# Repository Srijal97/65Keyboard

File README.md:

# 65Keyboard
Making a 65% Mechanical Keyboard

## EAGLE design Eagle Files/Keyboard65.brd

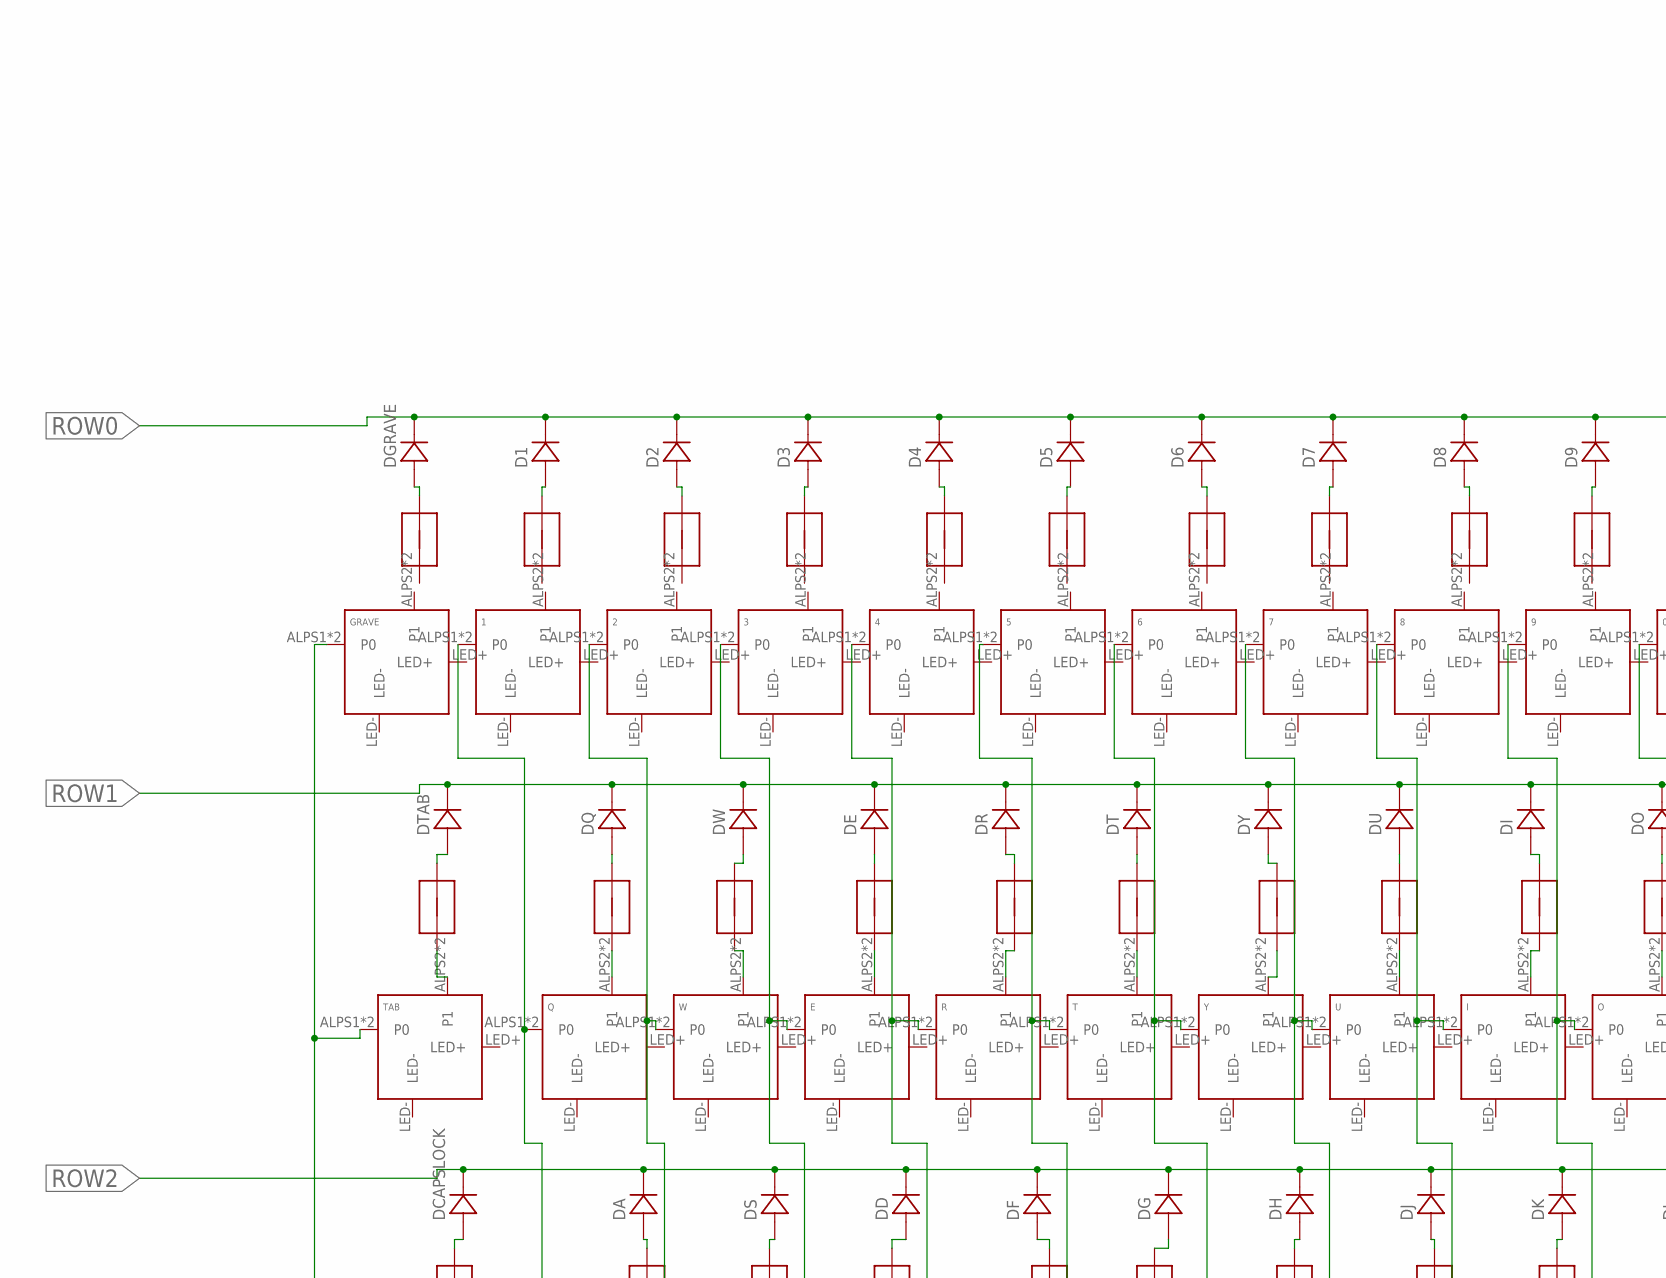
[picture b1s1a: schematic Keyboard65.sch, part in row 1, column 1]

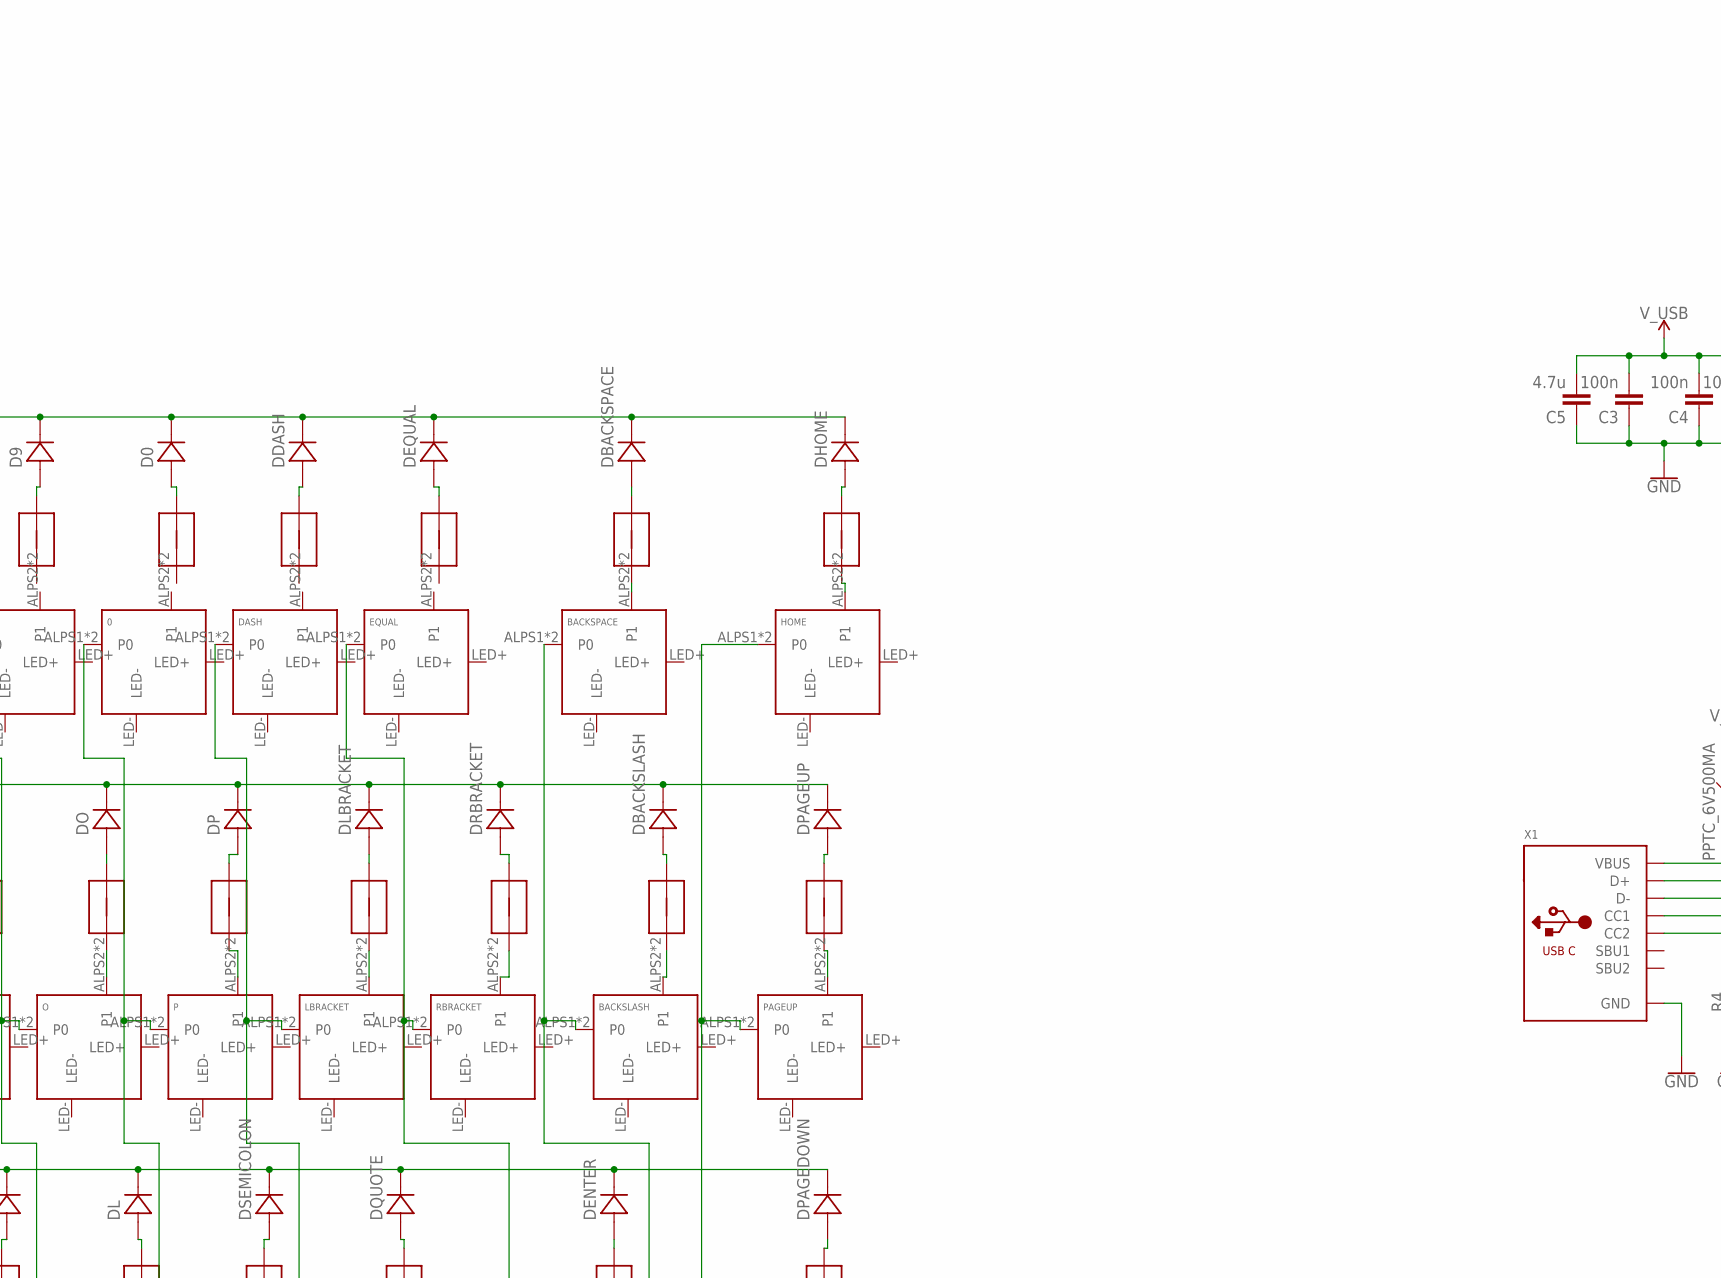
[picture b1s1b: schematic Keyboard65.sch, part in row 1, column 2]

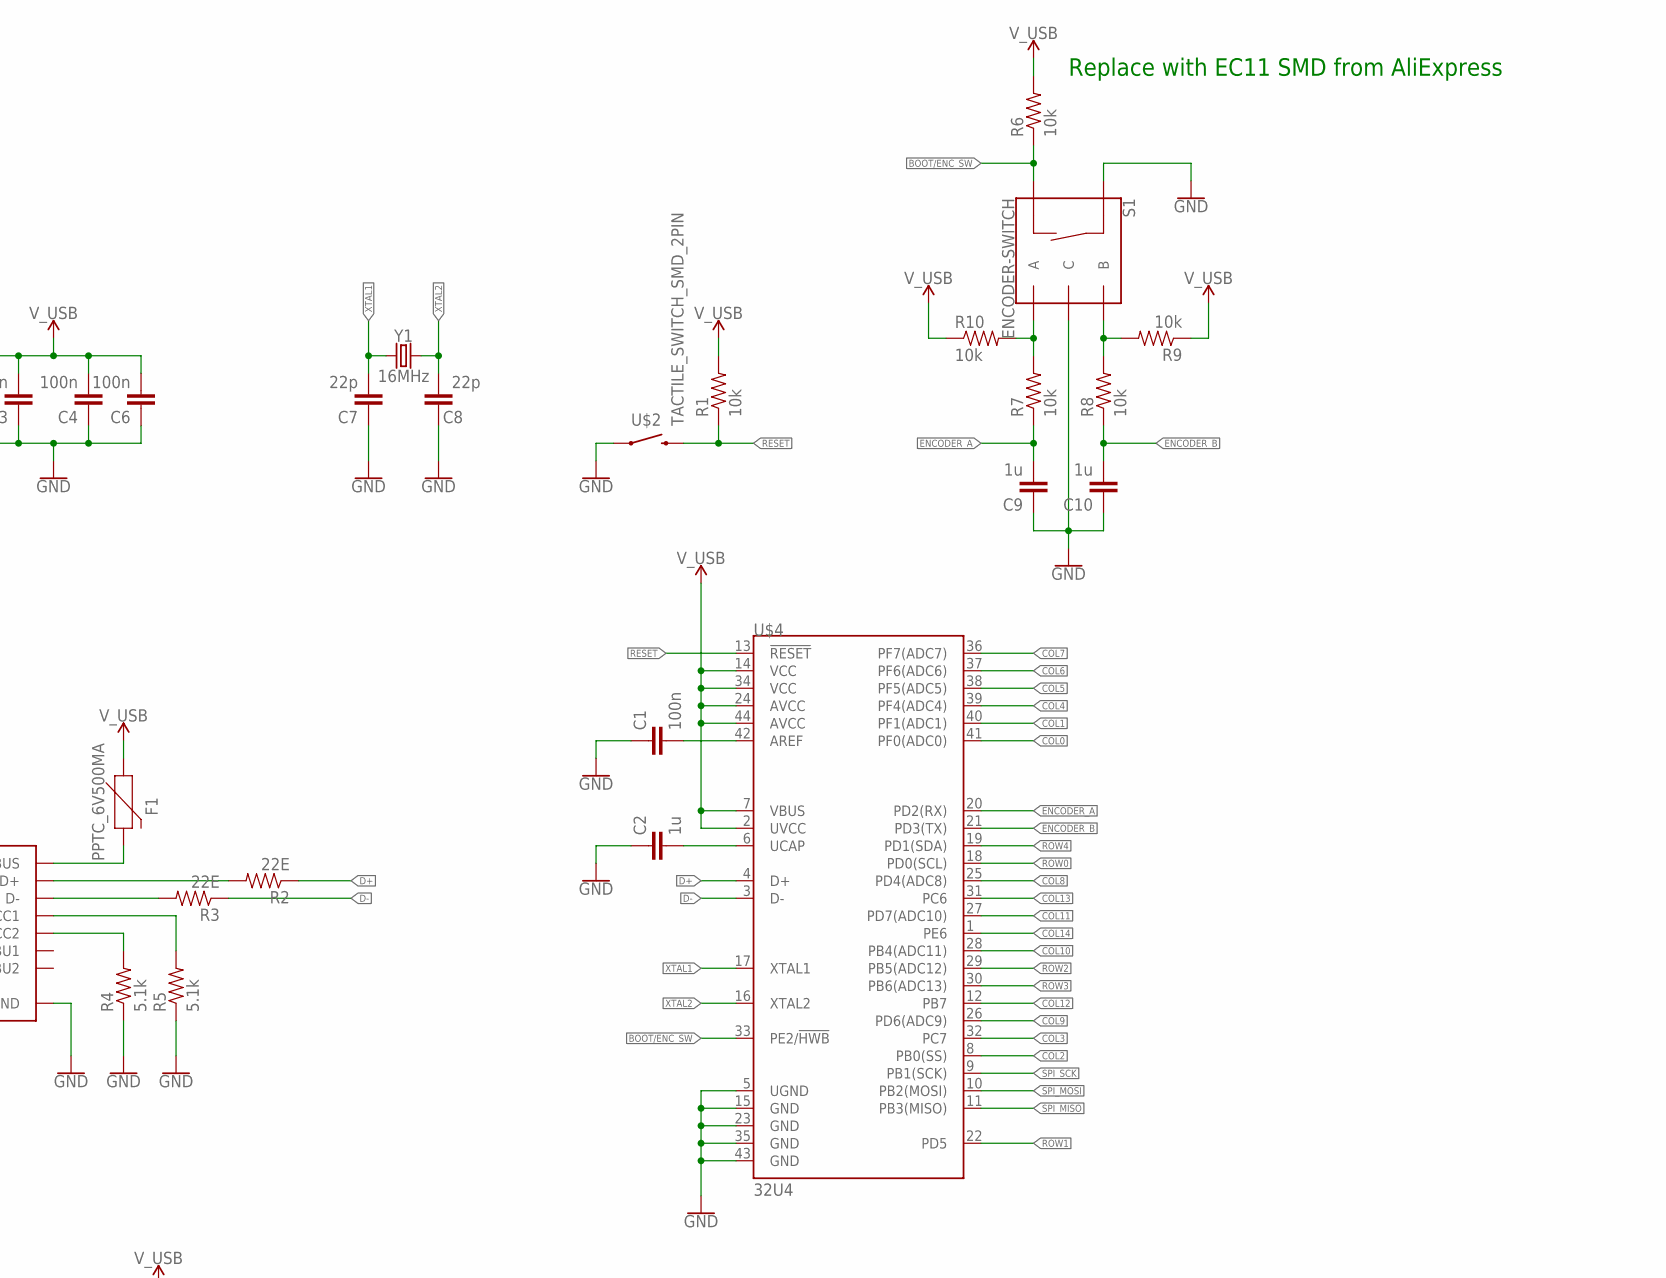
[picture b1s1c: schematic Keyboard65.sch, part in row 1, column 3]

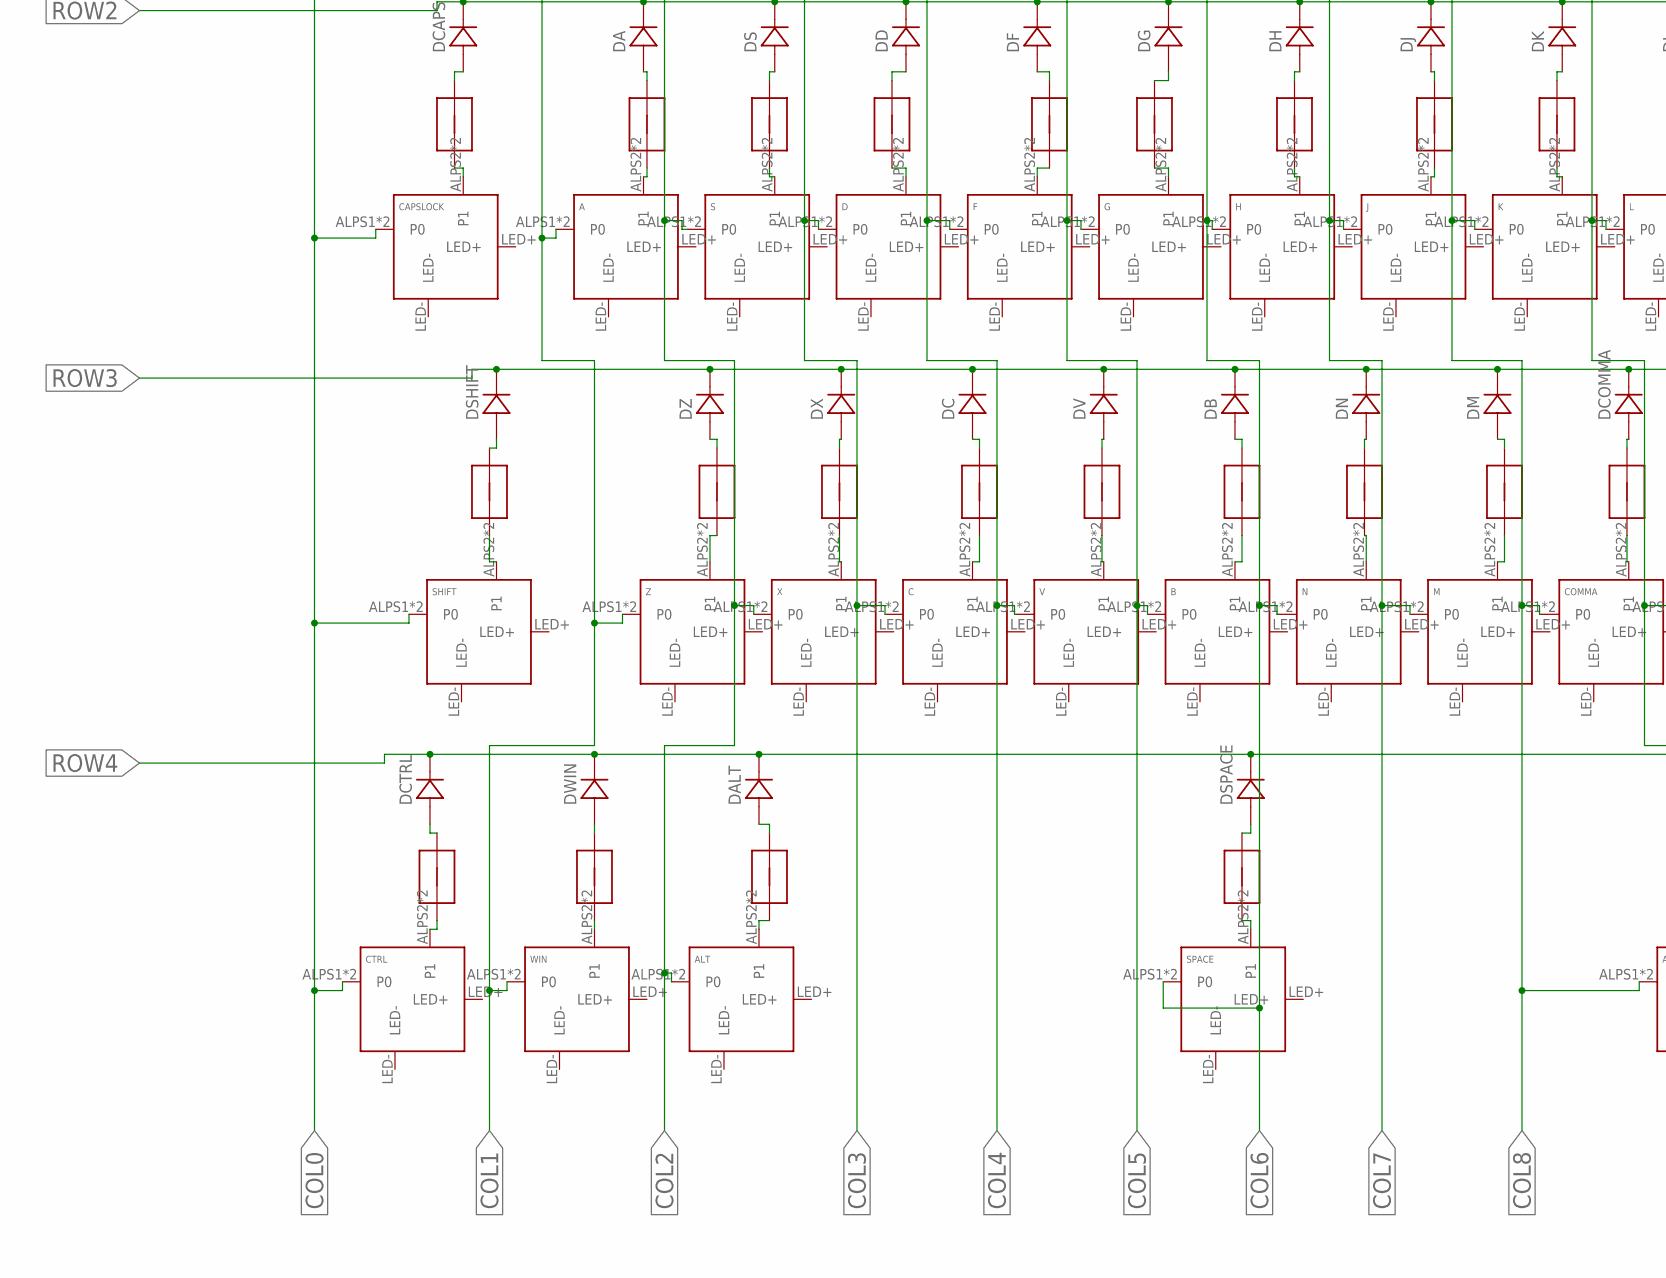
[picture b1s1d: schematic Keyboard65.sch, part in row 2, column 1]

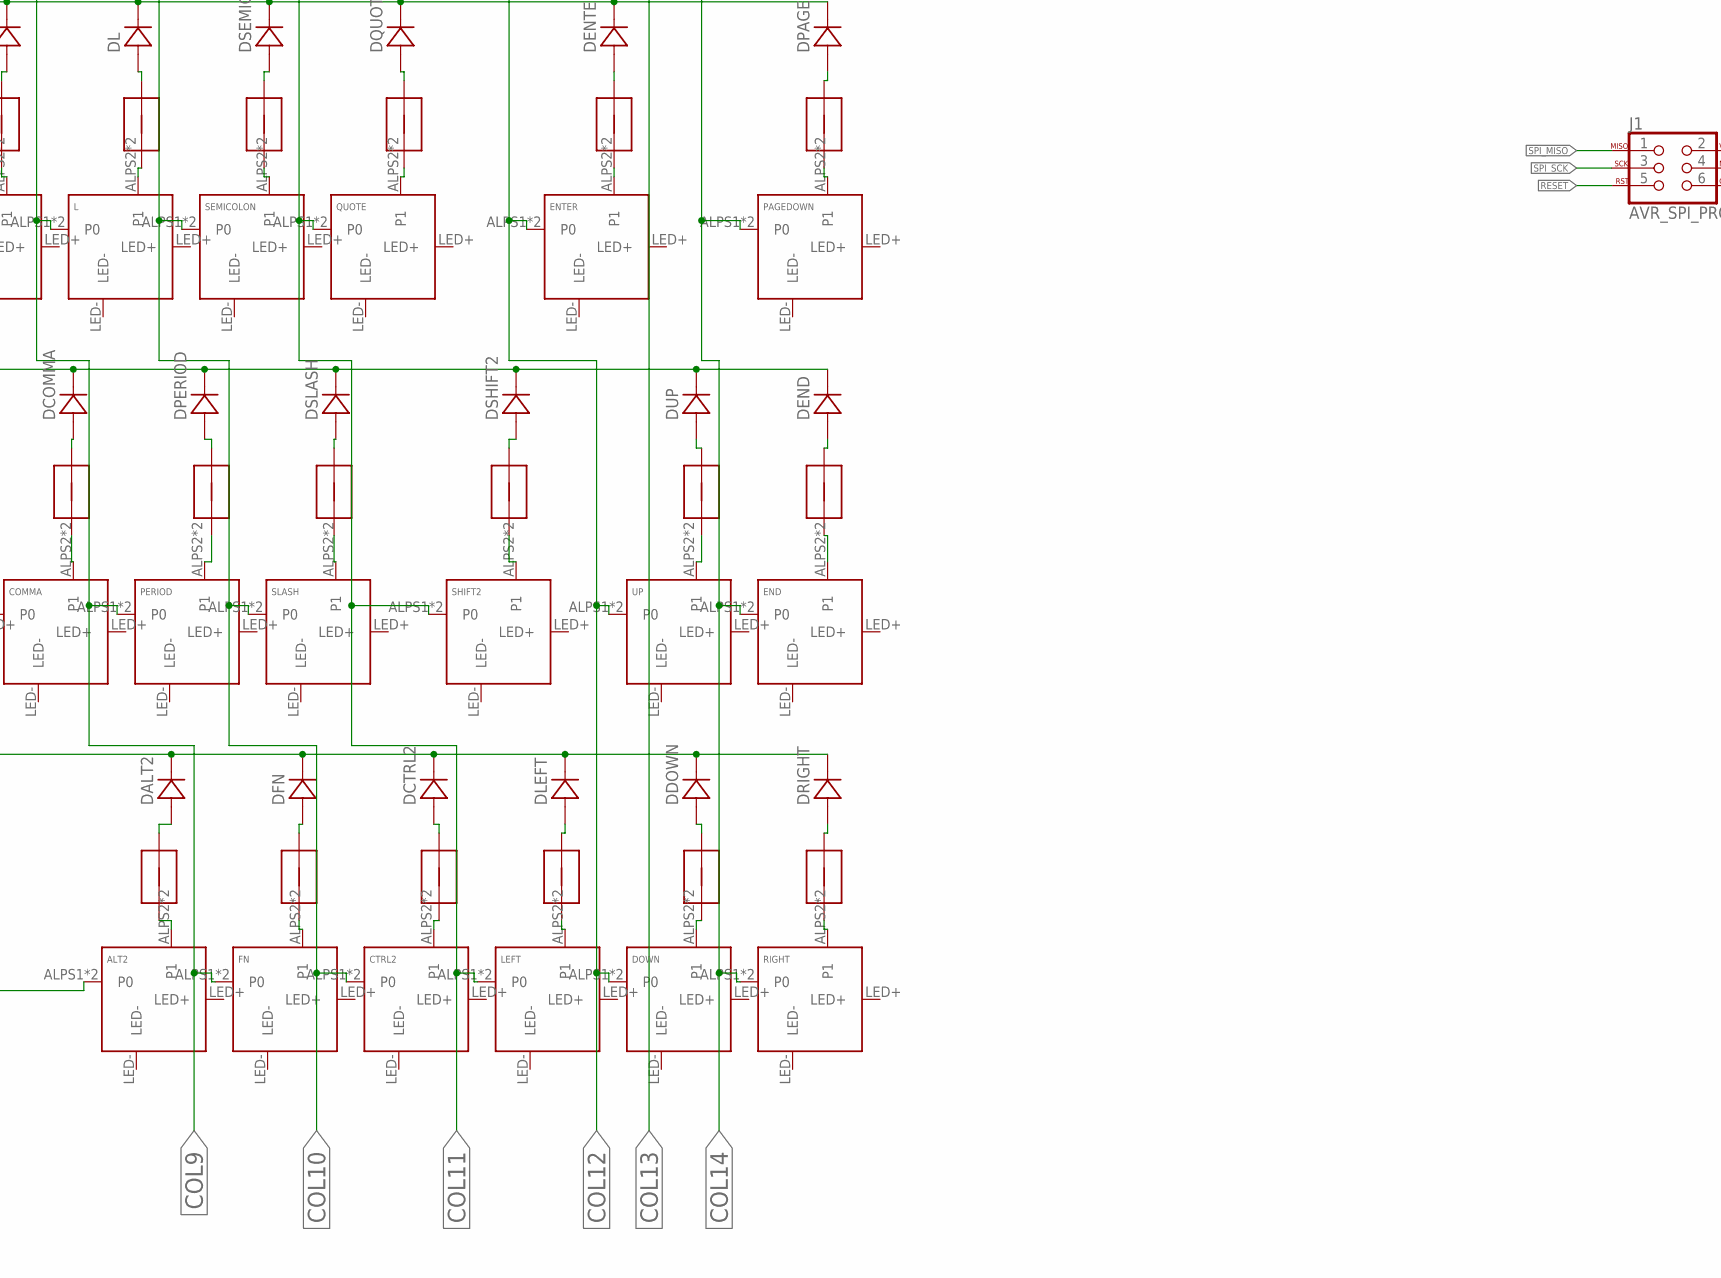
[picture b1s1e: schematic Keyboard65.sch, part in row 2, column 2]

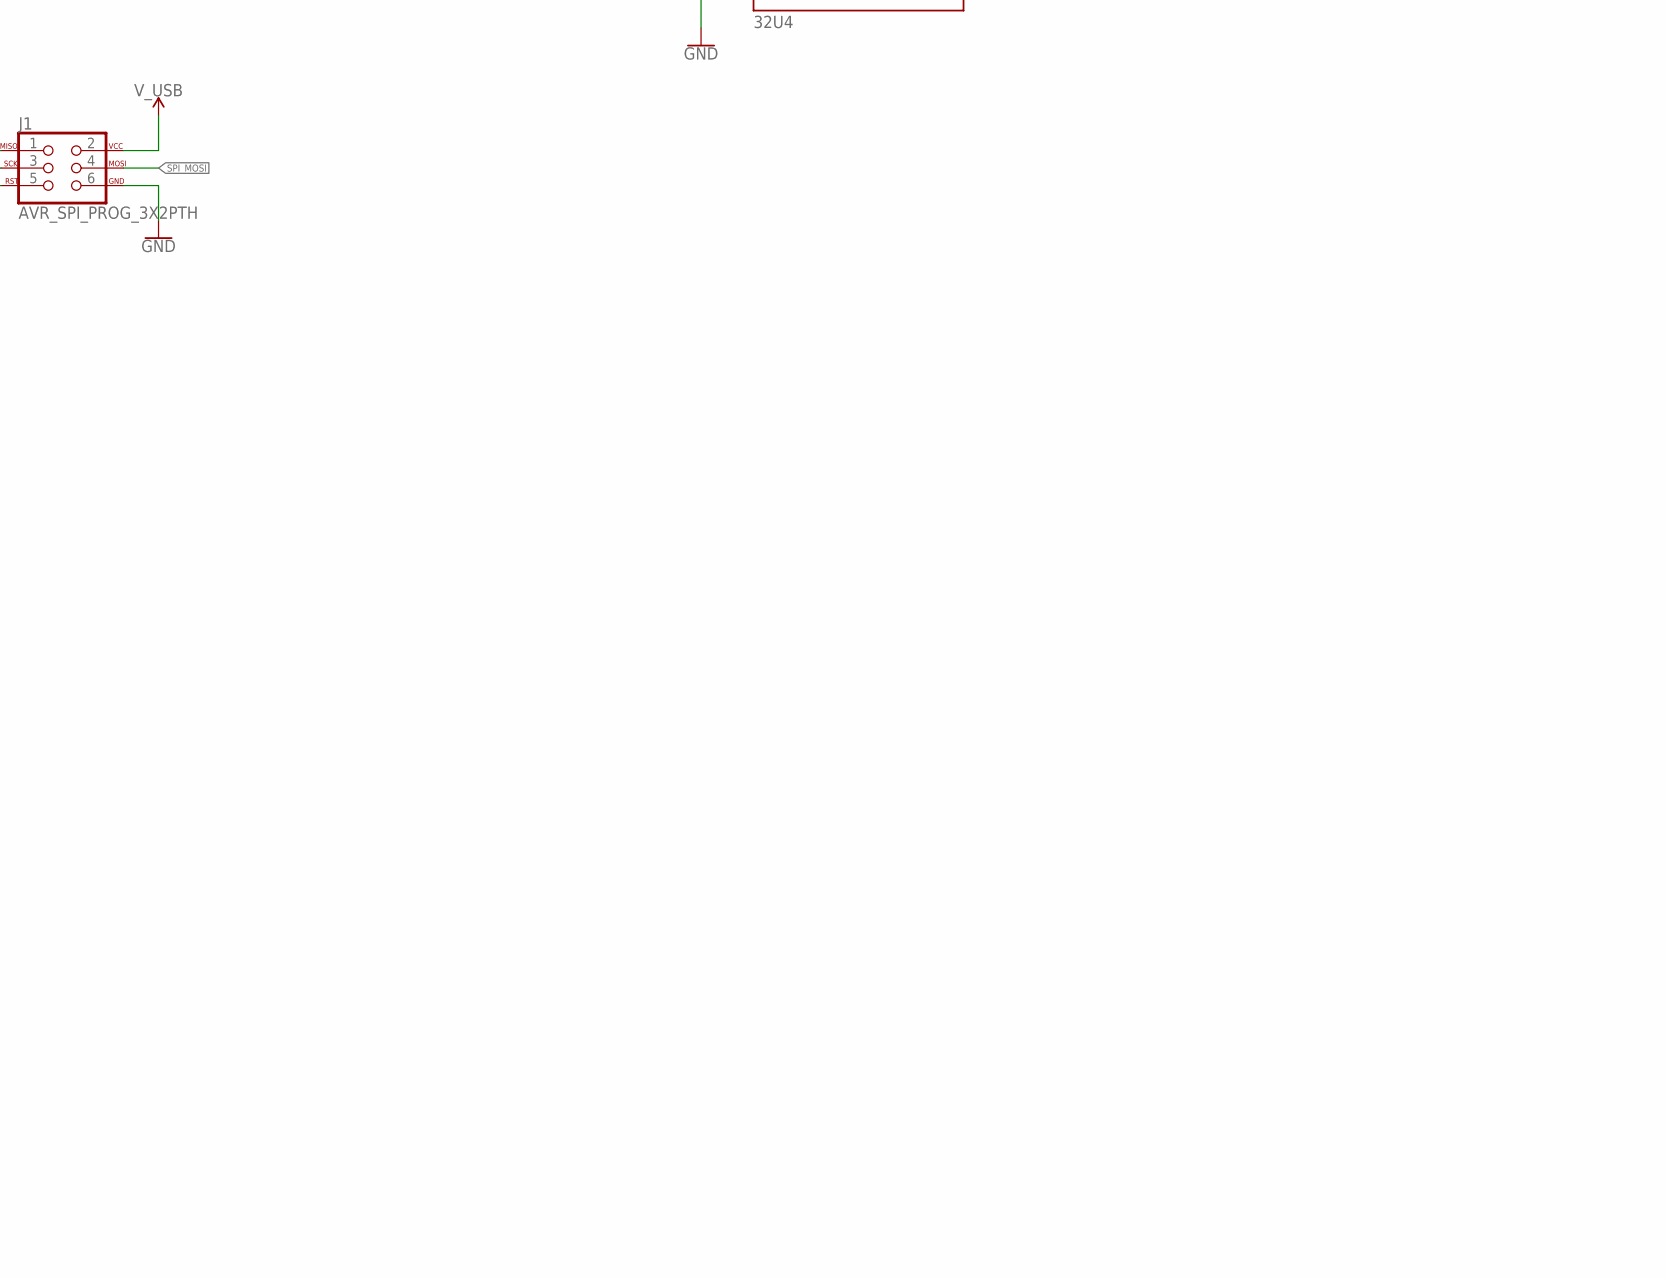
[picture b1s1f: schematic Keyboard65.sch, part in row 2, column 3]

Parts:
0, 1, 2, 3, 4, 5, 6, 7, 8, 9: KEYSWITCH-LED-ALPSMX-1U-LED; ALPSMX-1U-LED
A: KEYSWITCH-LED-ALPSMX-1U-LED; ALPSMX-1U-LED
ALT, ALT2: KEYSWITCH-LED-ALPSMX-1U-LED; ALPSMX-1U-LED
B: KEYSWITCH-LED-ALPSMX-1U-LED; ALPSMX-1U-LED
BACKSLASH: KEYSWITCH-LED-ALPSMX-1U-LED; ALPSMX-1U-LED
BACKSPACE: KEYSWITCH-LED-ALPSMX-2U-LED; ALPSMX-2U-LED
C: KEYSWITCH-LED-ALPSMX-1U-LED; ALPSMX-1U-LED
C1, C3, C4, C6: 100n; 0805
C2, C9, C10: 1u; 0805
C5: 4.7u; 0805
C7, C8: 22p; 0805
CAPSLOCK: KEYSWITCH-LED-ALPSMX-1U-LED; ALPSMX-1U-LED
COMMA: KEYSWITCH-LED-ALPSMX-1U-LED; ALPSMX-1U-LED
CTRL, CTRL2: KEYSWITCH-LED-ALPSMX-1U-LED; ALPSMX-1U-LED
D: KEYSWITCH-LED-ALPSMX-1U-LED; ALPSMX-1U-LED
D0, D1, D2, D3, D4, D5, D6, D7, D8, D9: DIODE-SOD-123; SOD-123
DA: DIODE-SOD-123; SOD-123
DALT, DALT2: DIODE-SOD-123; SOD-123
DASH: KEYSWITCH-LED-ALPSMX-1U-LED; ALPSMX-1U-LED
DB: DIODE-SOD-123; SOD-123
DBACKSLASH: DIODE-SOD-123; SOD-123
DBACKSPACE: DIODE-SOD-123; SOD-123
DC: DIODE-SOD-123; SOD-123
DCAPSLOCK: DIODE-SOD-123; SOD-123
DCOMMA: DIODE-SOD-123; SOD-123
DCTRL, DCTRL2: DIODE-SOD-123; SOD-123
DD: DIODE-SOD-123; SOD-123
DDASH: DIODE-SOD-123; SOD-123
DDOWN: DIODE-SOD-123; SOD-123
DE: DIODE-SOD-123; SOD-123
DEND: DIODE-SOD-123; SOD-123
DENTER: DIODE-SOD-123; SOD-123
DEQUAL: DIODE-SOD-123; SOD-123
DF: DIODE-SOD-123; SOD-123
DFN: DIODE-SOD-123; SOD-123
DG: DIODE-SOD-123; SOD-123
DGRAVE: DIODE-SOD-123; SOD-123
DH: DIODE-SOD-123; SOD-123
DHOME: DIODE-SOD-123; SOD-123
DI: DIODE-SOD-123; SOD-123
DJ: DIODE-SOD-123; SOD-123
DK: DIODE-SOD-123; SOD-123
DL: DIODE-SOD-123; SOD-123
DLBRACKET: DIODE-SOD-123; SOD-123
DLEFT: DIODE-SOD-123; SOD-123
DM: DIODE-SOD-123; SOD-123
DN: DIODE-SOD-123; SOD-123
DO: DIODE-SOD-123; SOD-123
DOWN: KEYSWITCH-LED-ALPSMX-1U-LED; ALPSMX-1U-LED
DP: DIODE-SOD-123; SOD-123
DPAGEDOWN: DIODE-SOD-123; SOD-123
DPAGEUP: DIODE-SOD-123; SOD-123
DPERIOD: DIODE-SOD-123; SOD-123
DQ: DIODE-SOD-123; SOD-123
DQUOTE: DIODE-SOD-123; SOD-123
DR: DIODE-SOD-123; SOD-123
DRBRACKET: DIODE-SOD-123; SOD-123
DRIGHT: DIODE-SOD-123; SOD-123
DS: DIODE-SOD-123; SOD-123
DSEMICOLON: DIODE-SOD-123; SOD-123
DSHIFT, DSHIFT2: DIODE-SOD-123; SOD-123
DSLASH: DIODE-SOD-123; SOD-123
DSPACE: DIODE-SOD-123; SOD-123
DT: DIODE-SOD-123; SOD-123
DTAB: DIODE-SOD-123; SOD-123
DU: DIODE-SOD-123; SOD-123
DUP: DIODE-SOD-123; SOD-123
DV: DIODE-SOD-123; SOD-123
DW: DIODE-SOD-123; SOD-123
DWIN: DIODE-SOD-123; SOD-123
DX: DIODE-SOD-123; SOD-123
DY: DIODE-SOD-123; SOD-123
DZ: DIODE-SOD-123; SOD-123
E: KEYSWITCH-LED-ALPSMX-1U-LED; ALPSMX-1U-LED
END: KEYSWITCH-LED-ALPSMX-1U-LED; ALPSMX-1U-LED
ENTER: KEYSWITCH-LED-ALPSMX-2U-LED; ALPSMX-2U-LED
EQUAL: KEYSWITCH-LED-ALPSMX-1U-LED; ALPSMX-1U-LED
F: KEYSWITCH-LED-ALPSMX-1U-LED; ALPSMX-1U-LED
F1: PPTC_6V500MA; 0805
FN: KEYSWITCH-LED-ALPSMX-1U-LED; ALPSMX-1U-LED
G: KEYSWITCH-LED-ALPSMX-1U-LED; ALPSMX-1U-LED
GRAVE: KEYSWITCH-LED-ALPSMX-1U-LED; ALPSMX-1U-LED
H: KEYSWITCH-LED-ALPSMX-1U-LED; ALPSMX-1U-LED
HOME: KEYSWITCH-LED-ALPSMX-1U-LED; ALPSMX-1U-LED
I: KEYSWITCH-LED-ALPSMX-1U-LED; ALPSMX-1U-LED
J: KEYSWITCH-LED-ALPSMX-1U-LED; ALPSMX-1U-LED
J1: AVR_SPI_PROG_3X2PTH; 2X3
K: KEYSWITCH-LED-ALPSMX-1U-LED; ALPSMX-1U-LED
L: KEYSWITCH-LED-ALPSMX-1U-LED; ALPSMX-1U-LED
LBRACKET: KEYSWITCH-LED-ALPSMX-1U-LED; ALPSMX-1U-LED
LEFT: KEYSWITCH-LED-ALPSMX-1U-LED; ALPSMX-1U-LED
M: KEYSWITCH-LED-ALPSMX-1U-LED; ALPSMX-1U-LED
N: KEYSWITCH-LED-ALPSMX-1U-LED; ALPSMX-1U-LED
O: KEYSWITCH-LED-ALPSMX-1U-LED; ALPSMX-1U-LED
P: KEYSWITCH-LED-ALPSMX-1U-LED; ALPSMX-1U-LED
PAGEDOWN: KEYSWITCH-LED-ALPSMX-1U-LED; ALPSMX-1U-LED
PAGEUP: KEYSWITCH-LED-ALPSMX-1U-LED; ALPSMX-1U-LED
PERIOD: KEYSWITCH-LED-ALPSMX-1U-LED; ALPSMX-1U-LED
Q: KEYSWITCH-LED-ALPSMX-1U-LED; ALPSMX-1U-LED
QUOTE: KEYSWITCH-LED-ALPSMX-1U-LED; ALPSMX-1U-LED
R: KEYSWITCH-LED-ALPSMX-1U-LED; ALPSMX-1U-LED
R1, R6, R7, R8, R9, R10: 10k; 0805
R2, R3: 22E; 0805
R4, R5: 5.1k; 0805
RBRACKET: KEYSWITCH-LED-ALPSMX-1U-LED; ALPSMX-1U-LED
RIGHT: KEYSWITCH-LED-ALPSMX-1U-LED; ALPSMX-1U-LED
S: KEYSWITCH-LED-ALPSMX-1U-LED; ALPSMX-1U-LED
S1: ENCODER-SWITCH; ROTARY_ENC_PLAIN
SEMICOLON: KEYSWITCH-LED-ALPSMX-1U-LED; ALPSMX-1U-LED
SHIFT: KEYSWITCH-LED-ALPSMX-2U-LED; ALPSMX-2U-LED
SHIFT2: KEYSWITCH-LED-ALPSMX-1U-LED; ALPSMX-1U-LED
SLASH: KEYSWITCH-LED-ALPSMX-1U-LED; ALPSMX-1U-LED
SPACE: KEYSWITCH-LED-ALPSMX-6.25U-LED; ALPSMX-6.25U-LED
T: KEYSWITCH-LED-ALPSMX-1U-LED; ALPSMX-1U-LED
TAB: KEYSWITCH-LED-ALPSMX-1U-LED; ALPSMX-1U-LED
U: KEYSWITCH-LED-ALPSMX-1U-LED; ALPSMX-1U-LED
U$1, U$3, U$5, U$6, U$7, U$8, U$9, U$10, U$11, U$12, U$13, U$14, U$15, U$16, U$17, U$18, U$19, U$20, U$21, U$22, U$23, U$24, U$25, U$26, U$27, U$28, U$29, U$30, U$31, U$32, U$33, U$34, U$35, U$36, U$37, U$38, U$39, U$40, U$41, U$42, U$43, U$44, U$45, U$46, U$47, U$48, U$49, U$50, U$51, U$52, U$53, U$54, U$55, U$56, U$57, U$58, U$59, U$60, U$61, U$62, U$63, U$64, U$65, U$66, U$67, U$68, U$69, U$70: KBD-SEPERATOR
U$2: TACTILE_SWITCH_SMD_2PIN
U$4: 32U4; QFN-44
UP: KEYSWITCH-LED-ALPSMX-1U-LED; ALPSMX-1U-LED
V: KEYSWITCH-LED-ALPSMX-1U-LED; ALPSMX-1U-LED
W: KEYSWITCH-LED-ALPSMX-1U-LED; ALPSMX-1U-LED
WIN: KEYSWITCH-LED-ALPSMX-1U-LED; ALPSMX-1U-LED
X: KEYSWITCH-LED-ALPSMX-1U-LED; ALPSMX-1U-LED
X1: MICROBUILDER_USB_CUSB-C-RECEPTACLE; MICROBUILDER_USB_C_CUSB31-CFM2AX-01-X
Y: KEYSWITCH-LED-ALPSMX-1U-LED; ALPSMX-1U-LED
Y1: 16MHz; CRYSTAL-SMD-5X3.2-4PAD
Z: KEYSWITCH-LED-ALPSMX-1U-LED; ALPSMX-1U-LED

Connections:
BOOT/ENC_SW: R6.1, S1.SW-, U$4.33 (PE2/!HWB)
COL0: CAPSLOCK.ALPS1 (P0), CAPSLOCK.MX1 (P0), CTRL.ALPS1 (P0), CTRL.MX1 (P0), GRAVE.ALPS1 (P0), GRAVE.MX1 (P0), SHIFT.ALPS1 (P0), SHIFT.MX1 (P0), TAB.ALPS1 (P0), TAB.MX1 (P0), U$4.41 (PF0(ADC0))
COL1: 1.ALPS1 (P0), 1.MX1 (P0), A.ALPS1 (P0), A.MX1 (P0), Q.ALPS1 (P0), Q.MX1 (P0), U$4.40 (PF1(ADC1)), WIN.ALPS1 (P0), WIN.MX1 (P0), Z.ALPS1 (P0), Z.MX1 (P0)
COL2: 2.ALPS1 (P0), 2.MX1 (P0), ALT.ALPS1 (P0), ALT.MX1 (P0), S.ALPS1 (P0), S.MX1 (P0), U$4.8 (PB0(SS)), W.ALPS1 (P0), W.MX1 (P0), X.ALPS1 (P0), X.MX1 (P0)
COL3: 3.ALPS1 (P0), 3.MX1 (P0), C.ALPS1 (P0), C.MX1 (P0), D.ALPS1 (P0), D.MX1 (P0), E.ALPS1 (P0), E.MX1 (P0), U$4.32 (PC7)
COL4: 4.ALPS1 (P0), 4.MX1 (P0), F.ALPS1 (P0), F.MX1 (P0), R.ALPS1 (P0), R.MX1 (P0), U$4.39 (PF4(ADC4)), V.ALPS1 (P0), V.MX1 (P0)
COL5: 5.ALPS1 (P0), 5.MX1 (P0), B.ALPS1 (P0), B.MX1 (P0), G.ALPS1 (P0), G.MX1 (P0), T.ALPS1 (P0), T.MX1 (P0), U$4.38 (PF5(ADC5))
COL6: 6.ALPS1 (P0), 6.MX1 (P0), H.ALPS1 (P0), H.MX1 (P0), N.ALPS1 (P0), N.MX1 (P0), SPACE.ALPS1 (P0), SPACE.MX1 (P0), U$4.37 (PF6(ADC6)), Y.ALPS1 (P0), Y.MX1 (P0)
COL7: 7.ALPS1 (P0), 7.MX1 (P0), J.ALPS1 (P0), J.MX1 (P0), M.ALPS1 (P0), M.MX1 (P0), U.ALPS1 (P0), U.MX1 (P0), U$4.36 (PF7(ADC7))
COL8: 8.ALPS1 (P0), 8.MX1 (P0), ALT2.ALPS1 (P0), ALT2.MX1 (P0), COMMA.ALPS1 (P0), COMMA.MX1 (P0), I.ALPS1 (P0), I.MX1 (P0), K.ALPS1 (P0), K.MX1 (P0), U$4.25 (PD4(ADC8))
COL9: 9.ALPS1 (P0), 9.MX1 (P0), FN.ALPS1 (P0), FN.MX1 (P0), L.ALPS1 (P0), L.MX1 (P0), O.ALPS1 (P0), O.MX1 (P0), PERIOD.ALPS1 (P0), PERIOD.MX1 (P0), U$4.26 (PD6(ADC9))
COL10: 0.ALPS1 (P0), 0.MX1 (P0), CTRL2.ALPS1 (P0), CTRL2.MX1 (P0), P.ALPS1 (P0), P.MX1 (P0), SEMICOLON.ALPS1 (P0), SEMICOLON.MX1 (P0), SLASH.ALPS1 (P0), SLASH.MX1 (P0), U$4.28 (PB4(ADC11))
COL11: DASH.ALPS1 (P0), DASH.MX1 (P0), LBRACKET.ALPS1 (P0), LBRACKET.MX1 (P0), LEFT.ALPS1 (P0), LEFT.MX1 (P0), QUOTE.ALPS1 (P0), QUOTE.MX1 (P0), SHIFT2.ALPS1 (P0), SHIFT2.MX1 (P0), U$4.27 (PD7(ADC10))
COL12: DOWN.ALPS1 (P0), DOWN.MX1 (P0), ENTER.ALPS1 (P0), ENTER.MX1 (P0), EQUAL.ALPS1 (P0), EQUAL.MX1 (P0), RBRACKET.ALPS1 (P0), RBRACKET.MX1 (P0), U$4.12 (PB7), UP.ALPS1 (P0), UP.MX1 (P0)
COL13: BACKSLASH.ALPS1 (P0), BACKSLASH.MX1 (P0), BACKSPACE.ALPS1 (P0), BACKSPACE.MX1 (P0), U$4.31 (PC6)
COL14: END.ALPS1 (P0), END.MX1 (P0), HOME.ALPS1 (P0), HOME.MX1 (P0), PAGEDOWN.ALPS1 (P0), PAGEDOWN.MX1 (P0), PAGEUP.ALPS1 (P0), PAGEUP.MX1 (P0), RIGHT.ALPS1 (P0), RIGHT.MX1 (P0), U$4.1 (PE6)
D+: R2.1, U$4.4 (D+)
D-: R3.1, U$4.3 (D-)
ENCODER_A: C9.2, R7.1, U$4.20 (PD2(RX))
ENCODER_B: C10.2, R8.1, U$4.21 (PD3(TX))
GND: C1.1, C2.1, C3.1, C4.1, C5.1, C6.1, C7.1, C8.1, C9.1, C10.1, J1.6, R4.1, R5.1, S1.C, S1.SW+, U$2.1, U$4.5 (UGND), U$4.15 (GND), U$4.23 (GND), U$4.35 (GND), U$4.43 (GND), X1.A1B12 (GND), X1.B1A12 (GND)
unnamed: CTRL.ALPS2 (P1), CTRL.MX2 (P1), U$1.2
unnamed: C2.2, U$4.6 (UCAP)
unnamed: C1.2, U$4.42 (AREF)
unnamed: R3.2, X1.A7 (D-), X1.B7 (D-)
unnamed: DCTRL.A, U$1.1
unnamed: RIGHT.ALPS2 (P1), RIGHT.MX2 (P1), U$12.2
unnamed: R2.2, X1.A6 (D+), X1.B6 (D+)
unnamed: R4.2, X1.B5 (CC2)
unnamed: R5.2, X1.A5 (CC1)
unnamed: HOME.ALPS2 (P1), HOME.MX2 (P1), U$70.2
unnamed: DHOME.A, U$70.1
unnamed: DBACKSPACE.A, U$69.1
unnamed: BACKSPACE.ALPS2 (P1), BACKSPACE.MX2 (P1), U$69.2
unnamed: DEQUAL.A, U$68.1
unnamed: DDASH.A, U$67.1
unnamed: D0.A, U$66.1
unnamed: D9.A, U$65.1
unnamed: D8.A, U$64.1
unnamed: D7.A, U$63.1
unnamed: D6.A, U$62.1
unnamed: D5.A, U$61.1
unnamed: D4.A, U$60.1
unnamed: D3.A, U$59.1
unnamed: D2.A, U$58.1
unnamed: TAB.ALPS2 (P1), TAB.MX2 (P1), U$41.2
unnamed: DTAB.A, U$41.1
unnamed: Q.ALPS2 (P1), Q.MX2 (P1), U$42.2
unnamed: DQ.A, U$42.1
unnamed: DW.A, U$43.1
unnamed: U$43.2, W.ALPS2 (P1), W.MX2 (P1)
unnamed: E.ALPS2 (P1), E.MX2 (P1), U$44.2
unnamed: DE.A, U$44.1
unnamed: DR.A, U$45.1
unnamed: R.ALPS2 (P1), R.MX2 (P1), U$45.2
unnamed: T.ALPS2 (P1), T.MX2 (P1), U$46.2
unnamed: DT.A, U$46.1
unnamed: DY.A, U$47.1
unnamed: U$47.2, Y.ALPS2 (P1), Y.MX2 (P1)
unnamed: U.ALPS2 (P1), U.MX2 (P1), U$48.2
unnamed: CAPSLOCK.ALPS2 (P1), CAPSLOCK.MX2 (P1), U$28.2
unnamed: DCAPSLOCK.A, U$28.1
unnamed: DA.A, U$27.1
unnamed: A.ALPS2 (P1), A.MX2 (P1), U$27.2
unnamed: S.ALPS2 (P1), S.MX2 (P1), U$29.2
unnamed: DS.A, U$29.1
unnamed: D.ALPS2 (P1), D.MX2 (P1), U$30.2
unnamed: DD.A, U$30.1
unnamed: DF.A, U$31.1
unnamed: F.ALPS2 (P1), F.MX2 (P1), U$31.2
unnamed: DG.A, U$32.1
unnamed: G.ALPS2 (P1), G.MX2 (P1), U$32.2
unnamed: H.ALPS2 (P1), H.MX2 (P1), U$33.2
unnamed: DH.A, U$33.1
unnamed: SHIFT.ALPS2 (P1), SHIFT.MX2 (P1), U$13.2
unnamed: DSHIFT.A, U$13.1
unnamed: U$14.2, Z.ALPS2 (P1), Z.MX2 (P1)
unnamed: DZ.A, U$14.1
unnamed: DX.A, U$15.1
unnamed: U$15.2, X.ALPS2 (P1), X.MX2 (P1)
unnamed: C.ALPS2 (P1), C.MX2 (P1), U$16.2
unnamed: DC.A, U$16.1
unnamed: DV.A, U$17.1
unnamed: U$17.2, V.ALPS2 (P1), V.MX2 (P1)
unnamed: B.ALPS2 (P1), B.MX2 (P1), U$18.2
unnamed: DB.A, U$18.1
unnamed: N.ALPS2 (P1), N.MX2 (P1), U$19.2
unnamed: DN.A, U$19.1
unnamed: DRIGHT.A, U$12.1
unnamed: DDOWN.A, U$11.1
unnamed: DOWN.ALPS2 (P1), DOWN.MX2 (P1), U$11.2
unnamed: LEFT.ALPS2 (P1), LEFT.MX2 (P1), U$10.2
unnamed: DLEFT.A, U$10.1
unnamed: DCTRL2.A, U$9.1
unnamed: CTRL2.ALPS2 (P1), CTRL2.MX2 (P1), U$9.2
unnamed: FN.ALPS2 (P1), FN.MX2 (P1), U$8.2
unnamed: DFN.A, U$8.1
unnamed: DALT2.A, U$7.1
unnamed: F1.2, X1.A4B9 (VBUS), X1.B4A9 (VBUS)
unnamed: R8.2, R9.2, S1.B
unnamed: R7.2, R10.2, S1.A
unnamed: ALT2.ALPS2 (P1), ALT2.MX2 (P1), U$7.2
unnamed: DSPACE.A, U$6.1
unnamed: SPACE.ALPS2 (P1), SPACE.MX2 (P1), U$6.2
unnamed: DWIN.A, U$3.1
unnamed: U$3.2, WIN.ALPS2 (P1), WIN.MX2 (P1)
unnamed: ALT.ALPS2 (P1), ALT.MX2 (P1), U$5.2
unnamed: DALT.A, U$5.1
unnamed: DM.A, U$20.1
unnamed: M.ALPS2 (P1), M.MX2 (P1), U$20.2
unnamed: COMMA.ALPS2 (P1), COMMA.MX2 (P1), U$21.2
unnamed: DCOMMA.A, U$21.1
unnamed: DPERIOD.A, U$22.1
unnamed: PERIOD.ALPS2 (P1), PERIOD.MX2 (P1), U$22.2
unnamed: SLASH.ALPS2 (P1), SLASH.MX2 (P1), U$23.2
unnamed: DSLASH.A, U$23.1
unnamed: SHIFT2.ALPS2 (P1), SHIFT2.MX2 (P1), U$24.2
unnamed: DSHIFT2.A, U$24.1
unnamed: U$25.2, UP.ALPS2 (P1), UP.MX2 (P1)
unnamed: DUP.A, U$25.1
unnamed: DEND.A, U$26.1
unnamed: END.ALPS2 (P1), END.MX2 (P1), U$26.2
unnamed: J.ALPS2 (P1), J.MX2 (P1), U$34.2
unnamed: DJ.A, U$34.1
unnamed: DK.A, U$35.1
unnamed: K.ALPS2 (P1), K.MX2 (P1), U$35.2
unnamed: L.ALPS2 (P1), L.MX2 (P1), U$36.2
unnamed: DL.A, U$36.1
unnamed: DSEMICOLON.A, U$37.1
unnamed: SEMICOLON.ALPS2 (P1), SEMICOLON.MX2 (P1), U$37.2
unnamed: QUOTE.ALPS2 (P1), QUOTE.MX2 (P1), U$38.2
unnamed: DQUOTE.A, U$38.1
unnamed: ENTER.ALPS2 (P1), ENTER.MX2 (P1), U$39.2
unnamed: DENTER.A, U$39.1
unnamed: DPAGEDOWN.A, U$40.1
unnamed: PAGEDOWN.ALPS2 (P1), PAGEDOWN.MX2 (P1), U$40.2
unnamed: DU.A, U$48.1
unnamed: DI.A, U$49.1
unnamed: I.ALPS2 (P1), I.MX2 (P1), U$49.2
unnamed: O.ALPS2 (P1), O.MX2 (P1), U$50.2
unnamed: DO.A, U$50.1
unnamed: DP.A, U$51.1
unnamed: P.ALPS2 (P1), P.MX2 (P1), U$51.2
unnamed: LBRACKET.ALPS2 (P1), LBRACKET.MX2 (P1), U$52.2
unnamed: DLBRACKET.A, U$52.1
unnamed: DRBRACKET.A, U$53.1
unnamed: RBRACKET.ALPS2 (P1), RBRACKET.MX2 (P1), U$53.2
unnamed: BACKSLASH.ALPS2 (P1), BACKSLASH.MX2 (P1), U$54.2
unnamed: DBACKSLASH.A, U$54.1
unnamed: DPAGEUP.A, U$55.1
unnamed: PAGEUP.ALPS2 (P1), PAGEUP.MX2 (P1), U$55.2
unnamed: D1.A, U$57.1
unnamed: DGRAVE.A, U$56.1
RESET: J1.5, R1.1, U$2.2, U$4.13 (!RESET)
ROW0: D0.C, D1.C, D2.C, D3.C, D4.C, D5.C, D6.C, D7.C, D8.C, D9.C, DBACKSPACE.C, DDASH.C, DEQUAL.C, DGRAVE.C, DHOME.C, U$4.18 (PD0(SCL))
ROW1: DBACKSLASH.C, DE.C, DI.C, DLBRACKET.C, DO.C, DP.C, DPAGEUP.C, DQ.C, DR.C, DRBRACKET.C, DT.C, DTAB.C, DU.C, DW.C, DY.C, U$4.22 (PD5)
ROW2: DA.C, DCAPSLOCK.C, DD.C, DENTER.C, DF.C, DG.C, DH.C, DJ.C, DK.C, DL.C, DPAGEDOWN.C, DQUOTE.C, DS.C, DSEMICOLON.C, U$4.29 (PB5(ADC12))
ROW3: DB.C, DC.C, DCOMMA.C, DEND.C, DM.C, DN.C, DPERIOD.C, DSHIFT.C, DSHIFT2.C, DSLASH.C, DUP.C, DV.C, DX.C, DZ.C, U$4.30 (PB6(ADC13))
ROW4: DALT.C, DALT2.C, DCTRL.C, DCTRL2.C, DDOWN.C, DFN.C, DLEFT.C, DRIGHT.C, DSPACE.C, DWIN.C, U$4.19 (PD1(SDA))
SPI_MISO: J1.1, U$4.11 (PB3(MISO))
SPI_MOSI: J1.4, U$4.10 (PB2(MOSI))
SPI_SCK: J1.3, U$4.9 (PB1(SCK))
V_USB: C3.2, C4.2, C5.2, C6.2, F1.1, J1.2, R1.2, R6.2, R9.1, R10.1, U$4.2 (UVCC), U$4.7 (VBUS), U$4.14 (VCC), U$4.24 (AVCC), U$4.34 (VCC), U$4.44 (AVCC)
XTAL1: C7.2, U$4.17 (XTAL1), Y1.1
XTAL2: C8.2, U$4.16 (XTAL2), Y1.3 (2)

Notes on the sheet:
Replace with EC11 SMD from AliExpress

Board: 2 copper layers, 231 parts (0 on the bottom side), 165 nets, no tracks yet.

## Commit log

2020-07-14 PCB schematics made, routing yet to be started

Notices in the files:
parts and their libraries:
SparkFun-Fuses: Licensing: Creative Commons ShareAlike 4.0 International - https://creativecommons.org/licenses/by-sa/4.0
